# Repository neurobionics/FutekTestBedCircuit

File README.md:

# FutekTestBedCircuit

#This Circuit is used to connect the 0-5VDC output of the Futek Load Cell to an i2c message within the 0-3.3V range such that a Raspberry Pi can read it

Relevant People to talk to:

- Riley Peiper
- Megan Giacobetti

Relevant Resources to Use:

- Circuit Layout (see KiCAD Schema File and IMG) 
- The KiCAD Schematic (see KiCAD Schema File)
- The KiCAD PCB Design
- JLC PCB Account [For Ordering] - reach out to @Japmanjeet Singh Gill for login details 
- BOM and CPL Files (See FinalOrderingPackage Folder)

*Note- if cannot login to JLC PCB Account, see the image " JLCPCB COMPONENT PNs " and copy PNs from that file. Note - connectors J1, J2, J3 not placed in the production files. 
- J1 and J2 are through-hole placement and J3 has part shortages in china

To place J3 MOLEX Connector (Mouser PN: 538-203558-0607):
- Get the stencil in the lab
- Apply solder paste to the J3 Connector Area
- Place connector
- Use a hot air heat gun until the solder paste is melted!

To place J1 and J2 Through Hole Connectors (Mouse PN: 651-1984620) 
- Do regular through-hole placement with solder
- Be careful not to solder the pins to the ground layer on the front of the board

**Female Connector for the J3 Molex - Mouser PN: 538-501330-0600**

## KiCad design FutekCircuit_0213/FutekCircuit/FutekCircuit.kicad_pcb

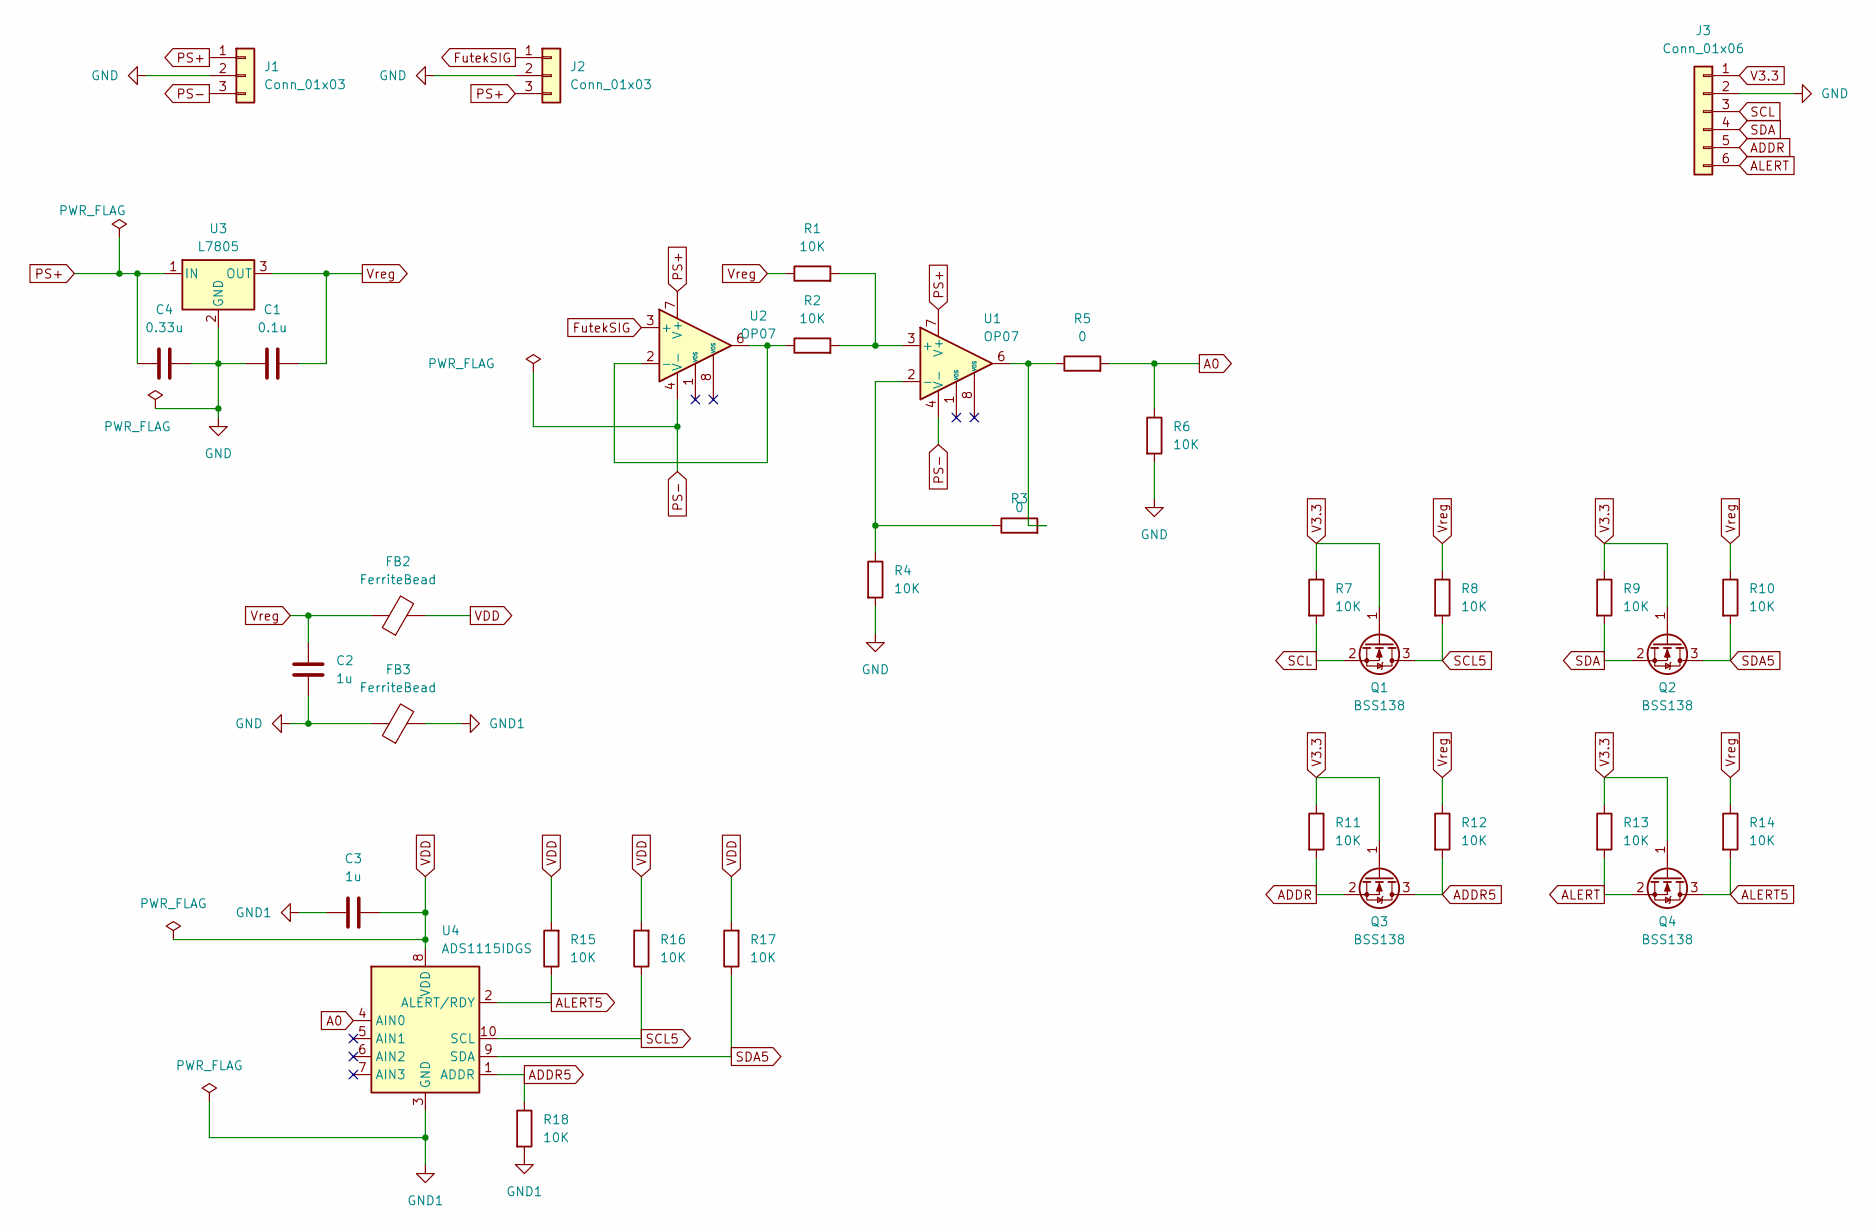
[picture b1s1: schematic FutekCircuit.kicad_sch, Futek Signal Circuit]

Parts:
C1: 0.1u; C_0603_1608Metric
C2, C3: 1u; C_0603_1608Metric
C4: 0.33u; C_0603_1608Metric
FB2, FB3: FerriteBead; BLM21AG102BH1J
J1, J2: Conn_01x03; CONN_1984620_PXC
J3: Conn_01x06; MOLEX_2035580607
Q1, Q2, Q3, Q4: BSS138; SOT-23-3
R1, R2, R4, R6, R7, R8, R9, R10, R11, R12, R13, R14, R15, R16, R17, R18: 10K; R_0603_1608Metric
R3, R5: 0; R_0603_1608Metric
U1, U2: OP07; SOIC127P600X175-8N
U3: L7805; D2PAK-STB35NF10T4
U4: ADS1115IDGS; VSSOP-10_3x3mm_P0.5mm

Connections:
A0: R5.2, R6.1, U4.4 (AIN0)
ADDR: J3.5, Q3.2 (S), R11.2
ADDR5: Q3.3 (D), R12.2, R18.1, U4.1 (ADDR)
ALERT: J3.6, Q4.2 (S), R13.2; also elsewhere on the board
ALERT5: Q4.3 (D), R14.2, R15.1, U4.2 (ALERT/RDY); also elsewhere on the board
FutekSIG: J2.1, U2.3 (+)
GND: C1.1, C2.2, C4.2, FB3.1, J1.2, J2.2, J3.2, R4.2, R6.2, U3.2 (GND)
GND1: C3.1, FB3.2, R18.2, U4.3 (GND)
unnamed: R3.2, R5.1, U1.6
unnamed: R1.2, R2.2, U1.3 (+)
unnamed: R3.1, R4.1, U1.2 (-)
unnamed: R2.1, U2.2 (-), U2.6
PS+: C4.1, J1.1, J2.3, U1.7 (V+), U2.7 (V+), U3.1 (IN)
PS-: J1.3, U1.4 (V-), U2.4 (V-)
SCL: J3.3, Q1.2 (S), R7.2
SCL5: Q1.3 (D), R8.2, R16.1, U4.10 (SCL)
SDA: J3.4, Q2.2 (S), R9.2
SDA5: Q2.3 (D), R10.2, R17.1, U4.9 (SDA)
V3.3: J3.1, Q1.1 (G), Q2.1 (G), Q3.1 (G), Q4.1 (G), R7.1, R9.1, R11.1, R13.1; also elsewhere on the board
VDD: C3.2, FB2.2, R15.2, R16.2, R17.2, U4.8 (VDD)
Vreg: C1.2, C2.1, FB2.1, R1.1, R8.1, R10.1, R12.1, R14.1, U3.3 (OUT)

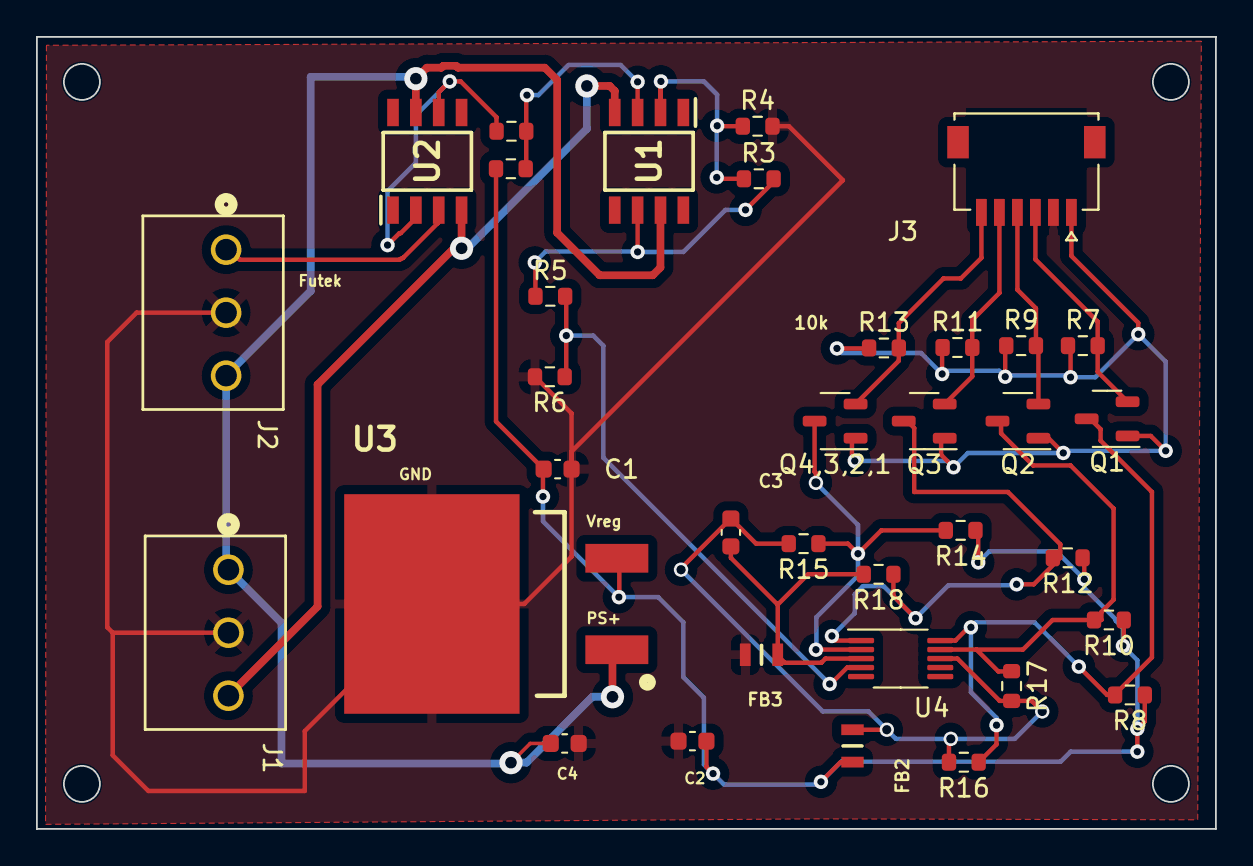
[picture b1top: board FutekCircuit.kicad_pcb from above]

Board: 2 copper layers, 65.5 x 44.0 mm, 35 parts (0 on the bottom side), 21 nets.

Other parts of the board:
Q4,3,2,1: BSS138; SOT-23-3

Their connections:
ALERT: Q4,3,2,1.2 (S); also elsewhere on the board
ALERT5: Q4,3,2,1.3 (D); also elsewhere on the board
V3.3: Q4,3,2,1.1 (G); also elsewhere on the board

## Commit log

2024-05-10 KiCAD Circuit Files
2024-05-10 Uploading Final Files
2024-05-10 Adding final files
2024-05-10 JLC PCB Component List
